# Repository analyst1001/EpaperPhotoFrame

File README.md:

# E-Paper Photo Frame

## Goals
- The main goal is to display photos on a E-paper display so that it looks similar to a photo frame. The displayed photo will change periodically.
- An additional goal is to allow the device to run on a common battery power source so that it can work without plugging into wall power.

## How to use
The script stored in `Software/transform_images.py` can be used to modify images in common format (png, jpg, etc.) to binary blobs which can be copied to a FAT32 partition (formatted with block size 512) on a SD card. These blobs are read by software starting with filename "0.bin", "1.bin", and so on and displayed on the E-paper screen. When a filename "<n>.bin" for some number `n` is not found, the software starts displaying images from "0.bin" again and keeps looping like this.

## Branches
This branch has PCB design to hold all the components for E-paper photo frame with connections to external battery, external E-paper display, external LEDs, and external SD card storage. Additionally it has code that can be flashed to STM32 MCU to use the PCB as an Epaper photo frame.
The branch `development_board` has code to run software on the development board with appropriate connections to external devices.

## MCU interfaces
- SPI interface is used to communicate with SD card and E-paper display.
- UART interface is used to log debug messages. This can be disabled by a C macro to reduce power usage in the final version.
- GPIOs to power on/off BUSY and ERROR LEDs, and SD card.

## Code implementation
1. Initialize the MCU using HAL layer. Configure system clock to use 80MHz. Using the max frequency allows SPI interface to SD card to communicate with max speed. This will allow SD card to be powered on for a shorter amount of time hence reducing the power usage (given that I plan to keep the MCU in low power mode for hours).
2. Initialize LEDs and RTC peripheral. BUSY LED indicates that the MCU is busy using the SD card or the E-paper display. ERROR LED indicates that an irrecoverable error has occurred. RTC peripheral is used to leverage the WakeUp timer in order to wake up the MCU from sleep mode periodically.
3. Initialize SD card and E-paper display.
4. Read data from the file to display and send it to E-paper display. Refresh the display and put it to sleep when the image is displayed.
5. Enable WakeUp interrupt to wake up the processor after given time interval.
6. Configure peripherals to reduce current consumption and put the MCU in Standby/Shutdown mode.

## Current consumption (TBD)

## Future Plans
- Use a data logger to measure instantaneous current consumption value with better resolution.
- Re-write the logic to use interrupt based processing. The SPI based communication can use interrupt based processing where the MCU can be put into low-power sleep mode when waiting for data transmission/reception. Same can be used when waiting for BUSY signal from E-paper display and time delays in the logic.
- Use DMA peripheral to transmit/receive large data blobs (image pixel data). STM32L4 series processor support a feature called Batch Acquisition sub-mode(BAM), as mentioned in Section 2.1.1 of [AN4621](https://www.st.com/resource/en/application_note/an4621-stm32l4-and-stm32l4-ultralowpower-features-overview-stmicroelectronics.pdf), that could allow this.

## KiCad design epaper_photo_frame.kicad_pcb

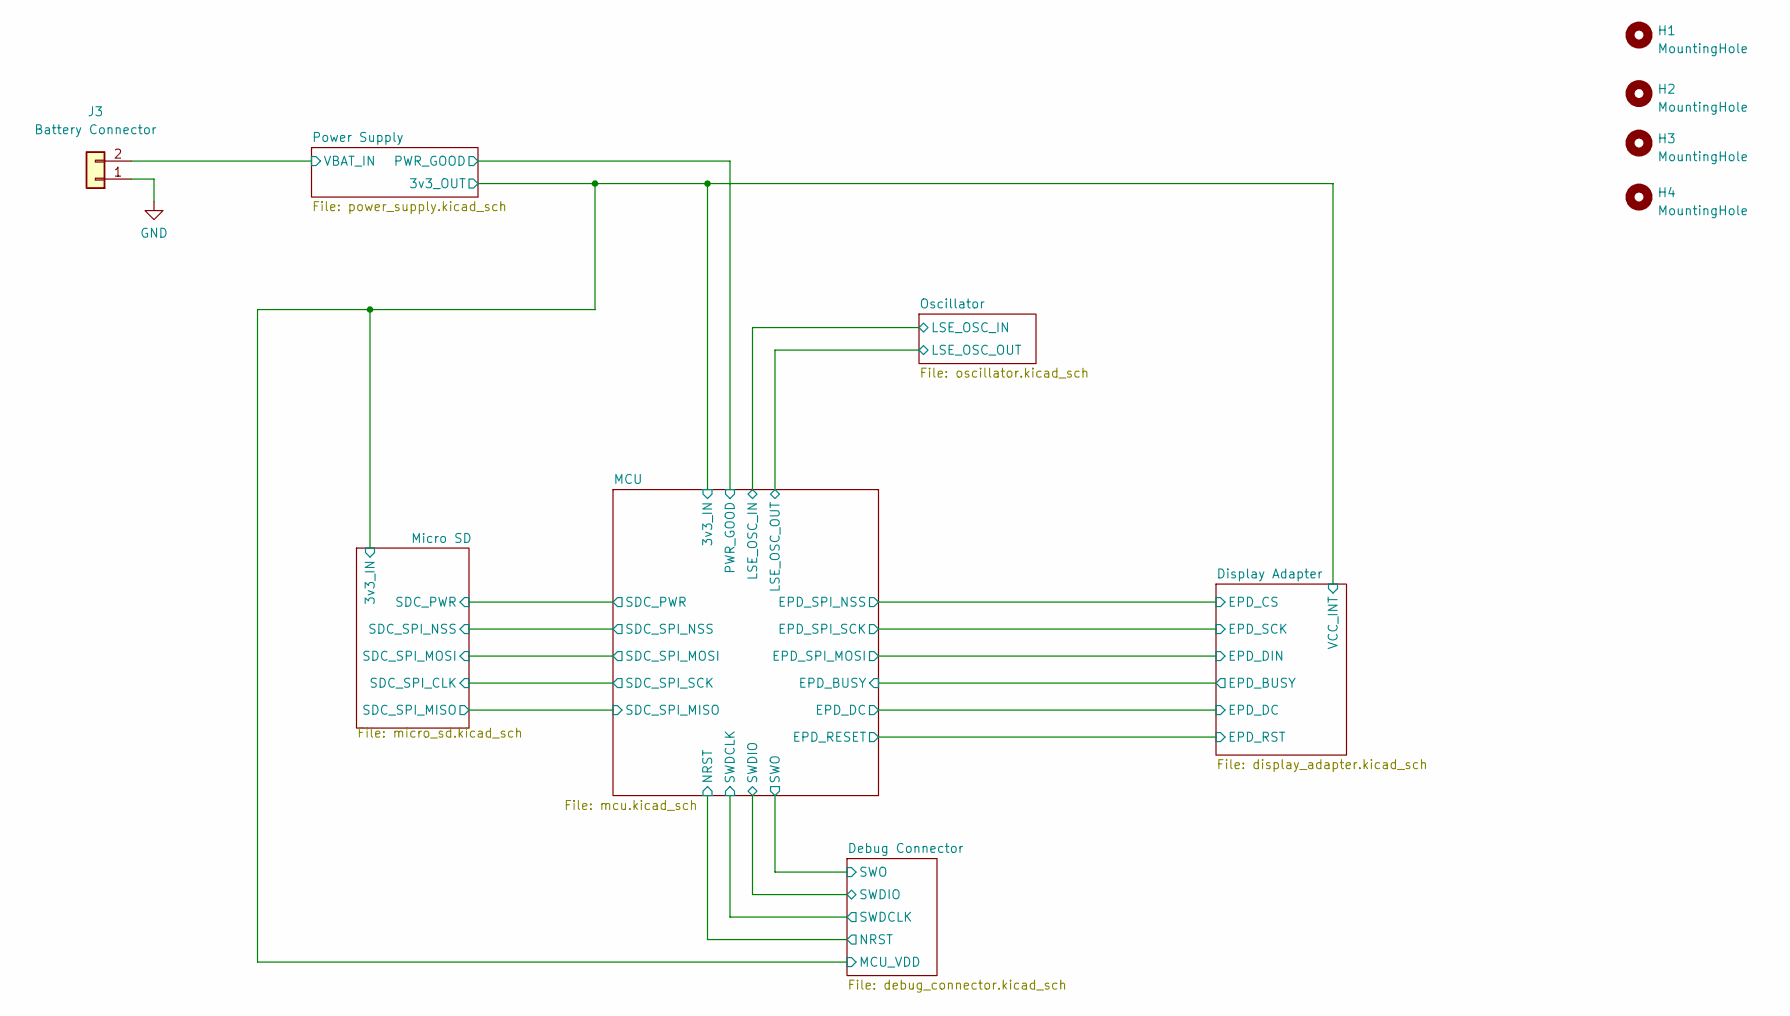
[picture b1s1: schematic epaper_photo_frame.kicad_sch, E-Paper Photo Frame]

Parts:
H1, H2, H3, H4: MountingHole; MountingHole_3.2mm_M3
J3: Battery Connector; JST_PH_B2B-PH-K_1x02_P2.00mm_Vertical

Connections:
/Power Supply/VBAT_IN: J3.2; also elsewhere on the board
GND: J3.1; also elsewhere on the board

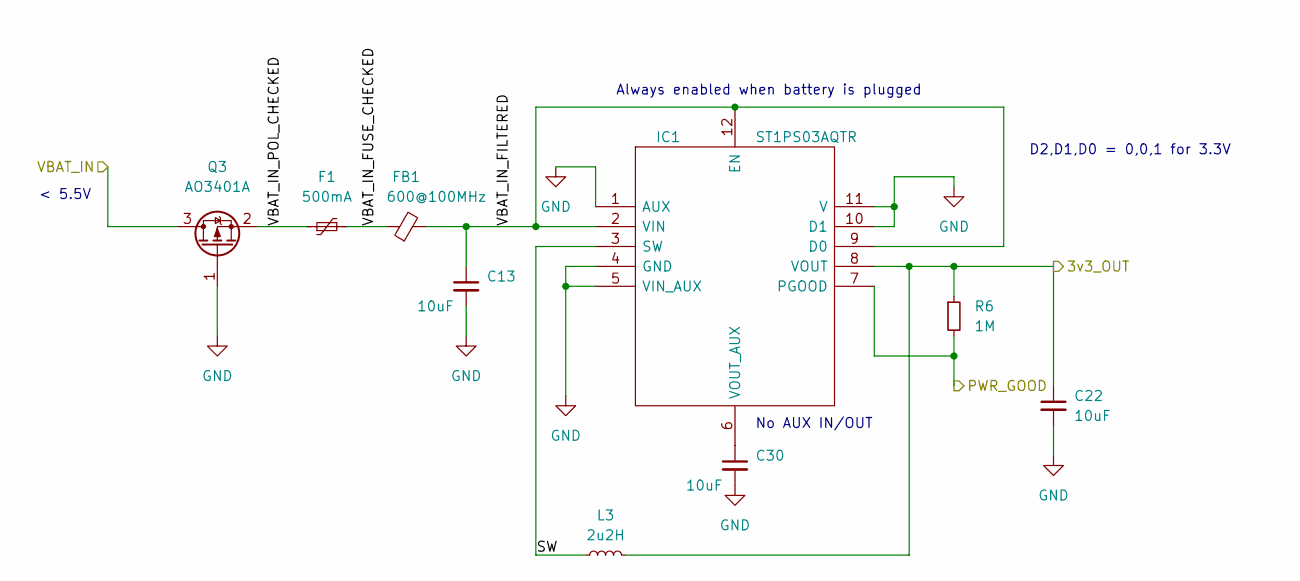
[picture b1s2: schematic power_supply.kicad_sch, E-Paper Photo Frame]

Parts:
C13, C22: 10uF; C_0805_2012Metric; LCSC C15850
C30: 10uF; C_0603_1608Metric; LCSC C96446
F1: 500mA; Fuse_1206_3216Metric; LCSC C69688
FB1: 600@100MHz; L_0805_2012Metric; LCSC C1017
IC1: ST1PS03AQTR; QFN40P170X200X55-12N-D; Manufacturer_Part_Number ST1PS03AQTR; Mouser Part Number 511-ST1PS03AQTR
L3: 2u2H; L_0805_2012Metric; LCSC C370034
Q3: AO3401A; SOT-23; LCSC C15127
R6: 1M; R_0805_2012Metric; LCSC C441966

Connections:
/Debug Connector/MCU_VDD: C22.1, IC1.8 (VOUT), L3.2, R6.1; also elsewhere on the board
/MCU/PWR_GOOD: IC1.7 (PGOOD), R6.2; also elsewhere on the board
/Power Supply/SW: IC1.3 (SW), L3.1
/Power Supply/VBAT_IN: Q3.3 (D); also elsewhere on the board
/Power Supply/VBAT_IN_FILTERED: C13.1, FB1.2, IC1.2 (VIN), IC1.9 (D0), IC1.12 (EN)
/Power Supply/VBAT_IN_FUSE_CHECKED: F1.2, FB1.1
/Power Supply/VBAT_IN_POL_CHECKED: F1.1, Q3.2 (S)
GND: C13.2, C22.2, C30.2, IC1.1 (AUX), IC1.4 (GND), IC1.5 (VIN_AUX), IC1.10 (D1), IC1.11 (V), Q3.1 (G); also elsewhere on the board
unnamed: C30.1, IC1.6 (VOUT_AUX)

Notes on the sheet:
D2,D1,D0 = 0,0,1 for 3.3V
No AUX IN/OUT
< 5.5V
Always enabled when battery is plugged

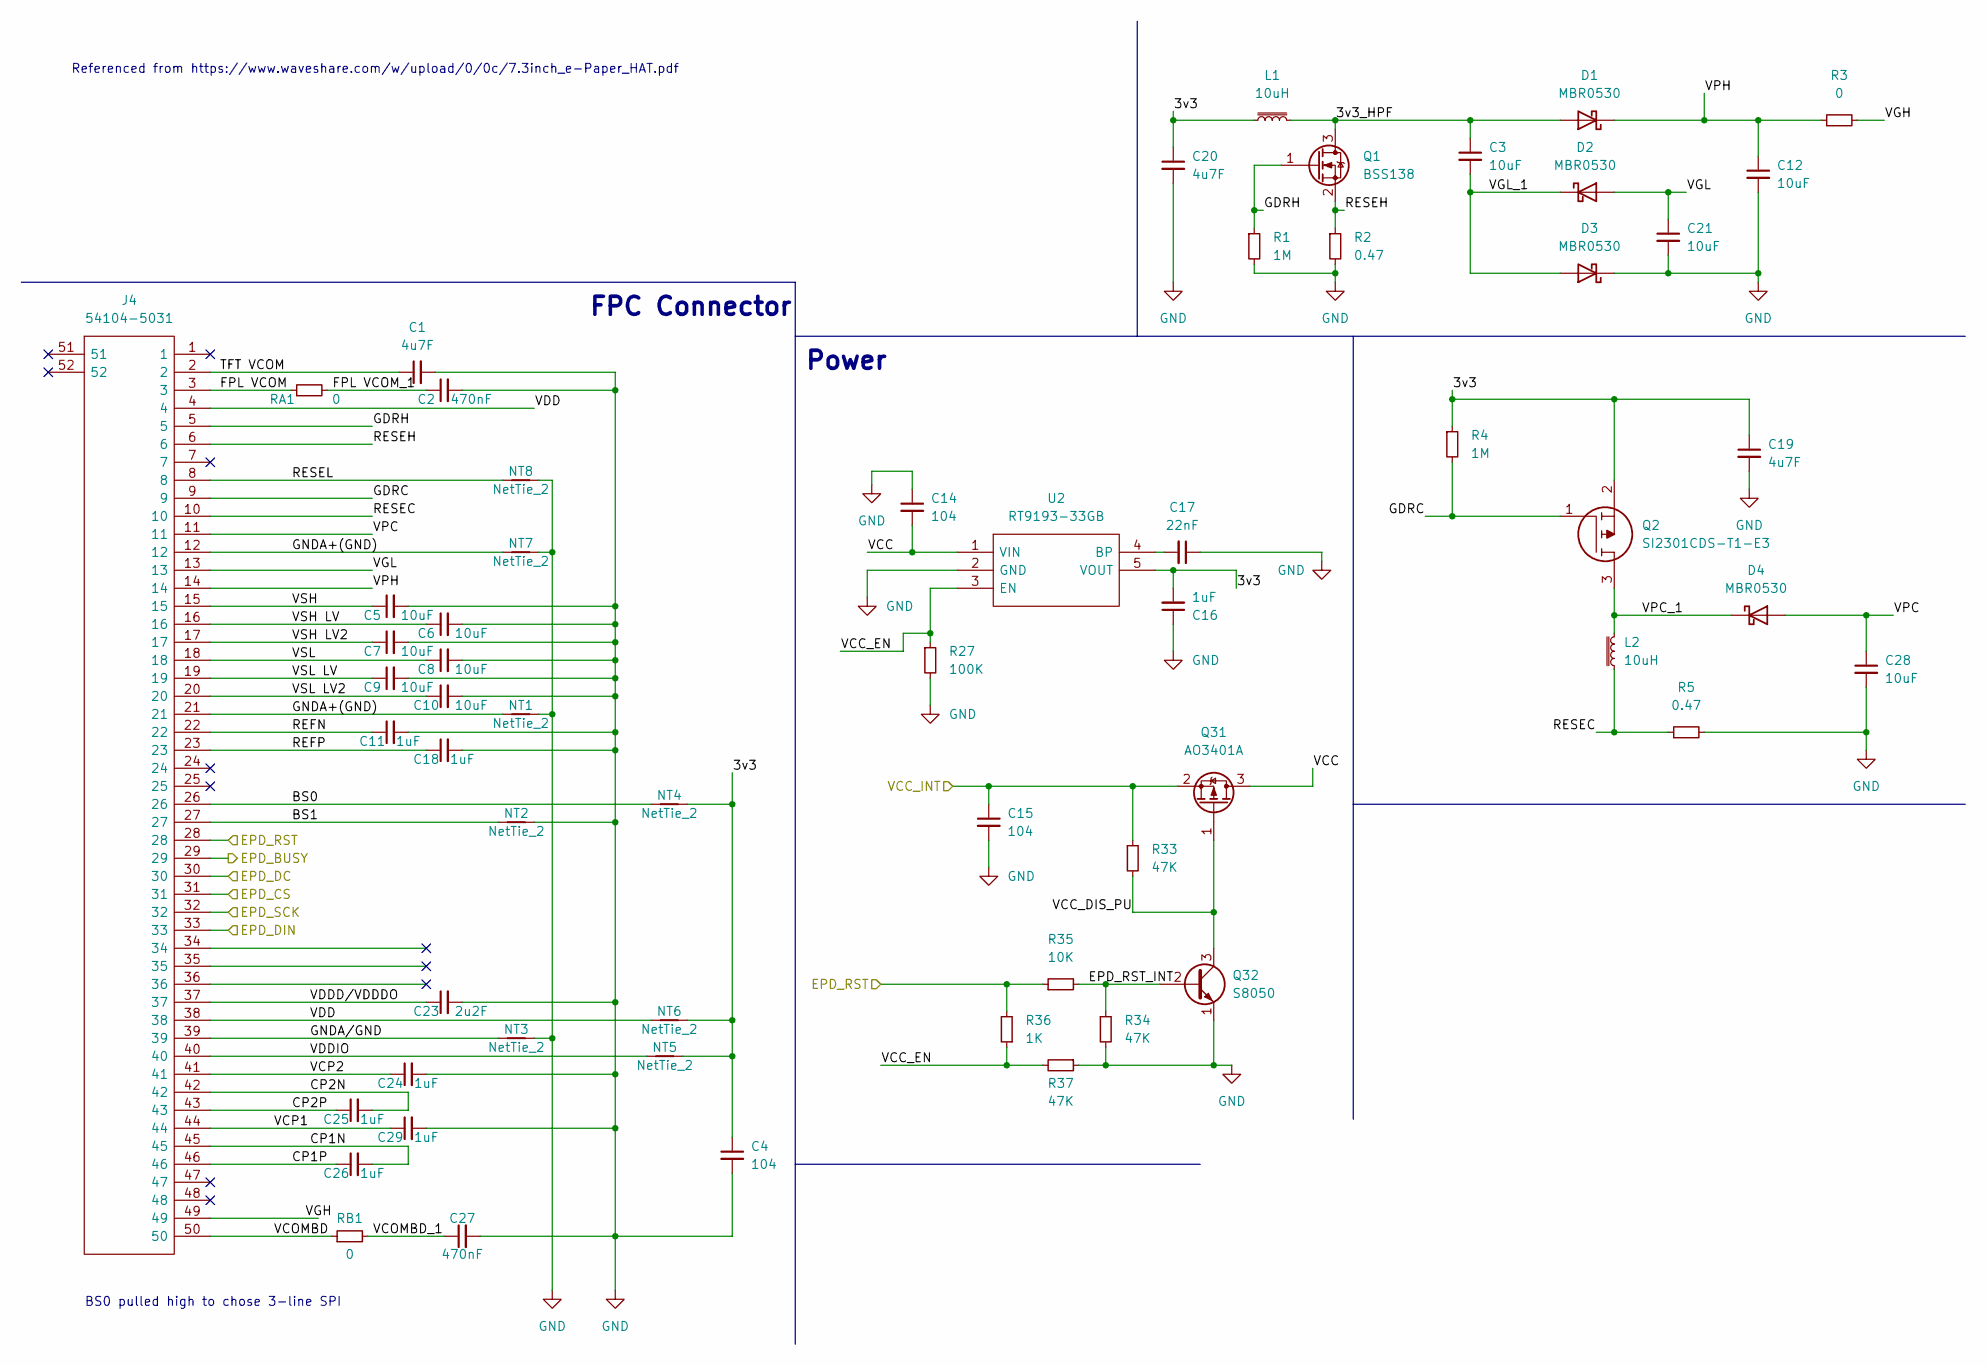
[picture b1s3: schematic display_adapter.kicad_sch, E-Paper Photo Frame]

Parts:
C1, C19, C20: 4u7F; C_0603_1608Metric; MAX Voltage 10V; LCSC C19666
C2, C27: 470nF; C_0603_1608Metric; MAX Voltage 25V; LCSC C1623
C3, C5, C6, C7, C8, C9, C10, C12, C21, C28: 10uF; C_0603_1608Metric; MAX Voltage 25V; LCSC C96446
C4: 104; C_0603_1608Metric; LCSC C14663
C11, C18, C24, C25, C26, C29: 1uF; C_0603_1608Metric; MAX Voltage 10V; LCSC C15849
C14, C15: 104; C_0805_2012Metric; LCSC C49678
C16: 1uF; C_0805_2012Metric; LCSC C28323
C17: 22nF; C_0805_2012Metric; LCSC C1729
C23: 2u2F; C_0603_1608Metric; MAX Voltage 6V; LCSC C23630
D1, D2, D3, D4: MBR0530; D_SOD-123; LCSC C18863
J4: 54104-5031; 541045031; Manufacturer_Part_Number 54104-5031; Mouser Part Number 538-54104-5031
L1, L2: 10uH; INDPM4040X200N; LCSC C82398
NT1, NT2, NT3, NT4, NT5, NT6, NT7, NT8: NetTie_2; NetTie-2_SMD_Pad0.5mm
Q1: BSS138; SOT-23; LCSC C82045
Q2: SI2301CDS-T1-E3; SOT95P237X112-3N; Manufacturer_Part_Number SI2301CDS-T1-E3; Mouser Part Number 781-SI2301CDS-E3
Q31: AO3401A; SOT-23; LCSC C15127
Q32: S8050; SOT-23-3; LCSC C2150
R1, R4: 1M; R_0805_2012Metric; LCSC C441966
R2, R5: 0.47; R_0805_2012Metric; LCSC C491238
R3: 0; R_0805_2012Metric; LCSC C17477
R27: 100K; R_0805_2012Metric; LCSC C149504
R33, R34: 47K; R_0805_2012Metric; LCSC C17713
R35: 10K; R_0805_2012Metric; LCSC C510098
R36: 1K; R_0805_2012Metric; LCSC C17513
R37: 47K; R_0805_2012Metric; LCSC C2073899
RA1: 0; R_0805_2012Metric; LCSC C17477
RB1: 0; R_0805_2012Metric; LCSC C17477
U2: RT9193-33GB; SOT94P279X130-5N; Manufacturer_Part_Number RT9193-33GB; LCSC C15651

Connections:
/Debug Connector/MCU_VDD: C15.1, Q31.2 (S), R33.1; also elsewhere on the board
/Display Adapter/3v3: C4.1, C16.2, C19.1, C20.1, L1.1, NT4.2, NT5.2, NT6.2, Q2.2, R4.1, U2.5 (VOUT)
/Display Adapter/3v3_HPF: C3.1, D1.2 (A), L1.2, Q1.3 (D)
/Display Adapter/BS0: J4.26, NT4.1
/Display Adapter/BS1: J4.27, NT2.1
/Display Adapter/CP1N: C26.2, J4.45
/Display Adapter/CP1P: C26.1, J4.46
/Display Adapter/CP2N: C25.2, J4.42
/Display Adapter/CP2P: C25.1, J4.43
/Display Adapter/EPD_BUSY: J4.29; also elsewhere on the board
/Display Adapter/EPD_CS: J4.31; also elsewhere on the board
/Display Adapter/EPD_DC: J4.30; also elsewhere on the board
/Display Adapter/EPD_DIN: J4.33; also elsewhere on the board
/Display Adapter/EPD_RST: J4.28, R35.1, R36.2; also elsewhere on the board
/Display Adapter/EPD_RST_INT: Q32.2 (B), R34.1, R35.2
/Display Adapter/EPD_SCK: J4.32; also elsewhere on the board
/Display Adapter/FPL VCOM: J4.3, RA1.1
/Display Adapter/FPL VCOM_1: C2.1, RA1.2
/Display Adapter/GDRC: J4.9, Q2.1, R4.2
/Display Adapter/GDRH: J4.5, Q1.1 (G), R1.1
/Display Adapter/GNDA+(GND): J4.12, J4.21, NT1.1, NT7.1
/Display Adapter/GNDA/GND: J4.39, NT3.1
/Display Adapter/REFN: C11.1, J4.22
/Display Adapter/REFP: C18.1, J4.23
/Display Adapter/RESEC: J4.10, L2.1, R5.1
/Display Adapter/RESEH: J4.6, Q1.2 (S), R2.1
/Display Adapter/RESEL: J4.8, NT8.1
/Display Adapter/TFT VCOM: C1.1, J4.2
/Display Adapter/VCC: C14.2, Q31.3 (D), U2.1 (VIN)
/Display Adapter/VCC_DIS_PU: Q31.1 (G), Q32.3 (C), R33.2
/Display Adapter/VCC_EN: R27.1, R36.1, R37.2, U2.3 (EN)
/Display Adapter/VCOMBD: J4.50, RB1.1
/Display Adapter/VCOMBD_1: C27.1, RB1.2
/Display Adapter/VCP1: C29.1, J4.44
/Display Adapter/VCP2: C24.1, J4.41
/Display Adapter/VDD: J4.4, J4.38, NT6.1
/Display Adapter/VDDD/VDDDO: C23.1, J4.37
/Display Adapter/VDDIO: J4.40, NT5.1
/Display Adapter/VGH: J4.49, R3.2
/Display Adapter/VGL: C21.1, D2.2 (A), J4.13
/Display Adapter/VGL_1: C3.2, D2.1 (K), D3.2 (A)
/Display Adapter/VPC: C28.1, D4.2 (A), J4.11
/Display Adapter/VPC_1: D4.1 (K), L2.2, Q2.3
/Display Adapter/VPH: C12.1, D1.1 (K), J4.14, R3.1
/Display Adapter/VSH: C5.1, J4.15
/Display Adapter/VSH LV: C6.1, J4.16
/Display Adapter/VSH LV2: C7.1, J4.17
/Display Adapter/VSL: C8.1, J4.18
/Display Adapter/VSL LV: C9.1, J4.19
/Display Adapter/VSL LV2: C10.1, J4.20
GND: C1.2, C2.2, C4.2, C5.2, C6.2, C7.2, C8.2, C9.2, C10.2, C11.2, C12.2, C14.1, C15.2, C16.1, C17.1, C18.2, C19.2, C20.2, C21.2, C23.2, C24.2, C27.2, C28.2, C29.2, D3.1 (K), NT1.2, NT2.2, NT3.2, NT7.2, NT8.2, Q32.1 (E), R1.2, R2.2, R5.2, R27.2, R34.2, R37.1, U2.2 (GND); also elsewhere on the board
unnamed: C17.2, U2.4 (BP)

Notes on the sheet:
FPC Connector
BS0 pulled high to chose 3-line SPI
Power
Referenced from https://www.waveshare.com/w/upload/0/0c/7.3inch_e-Paper_HAT.pdf

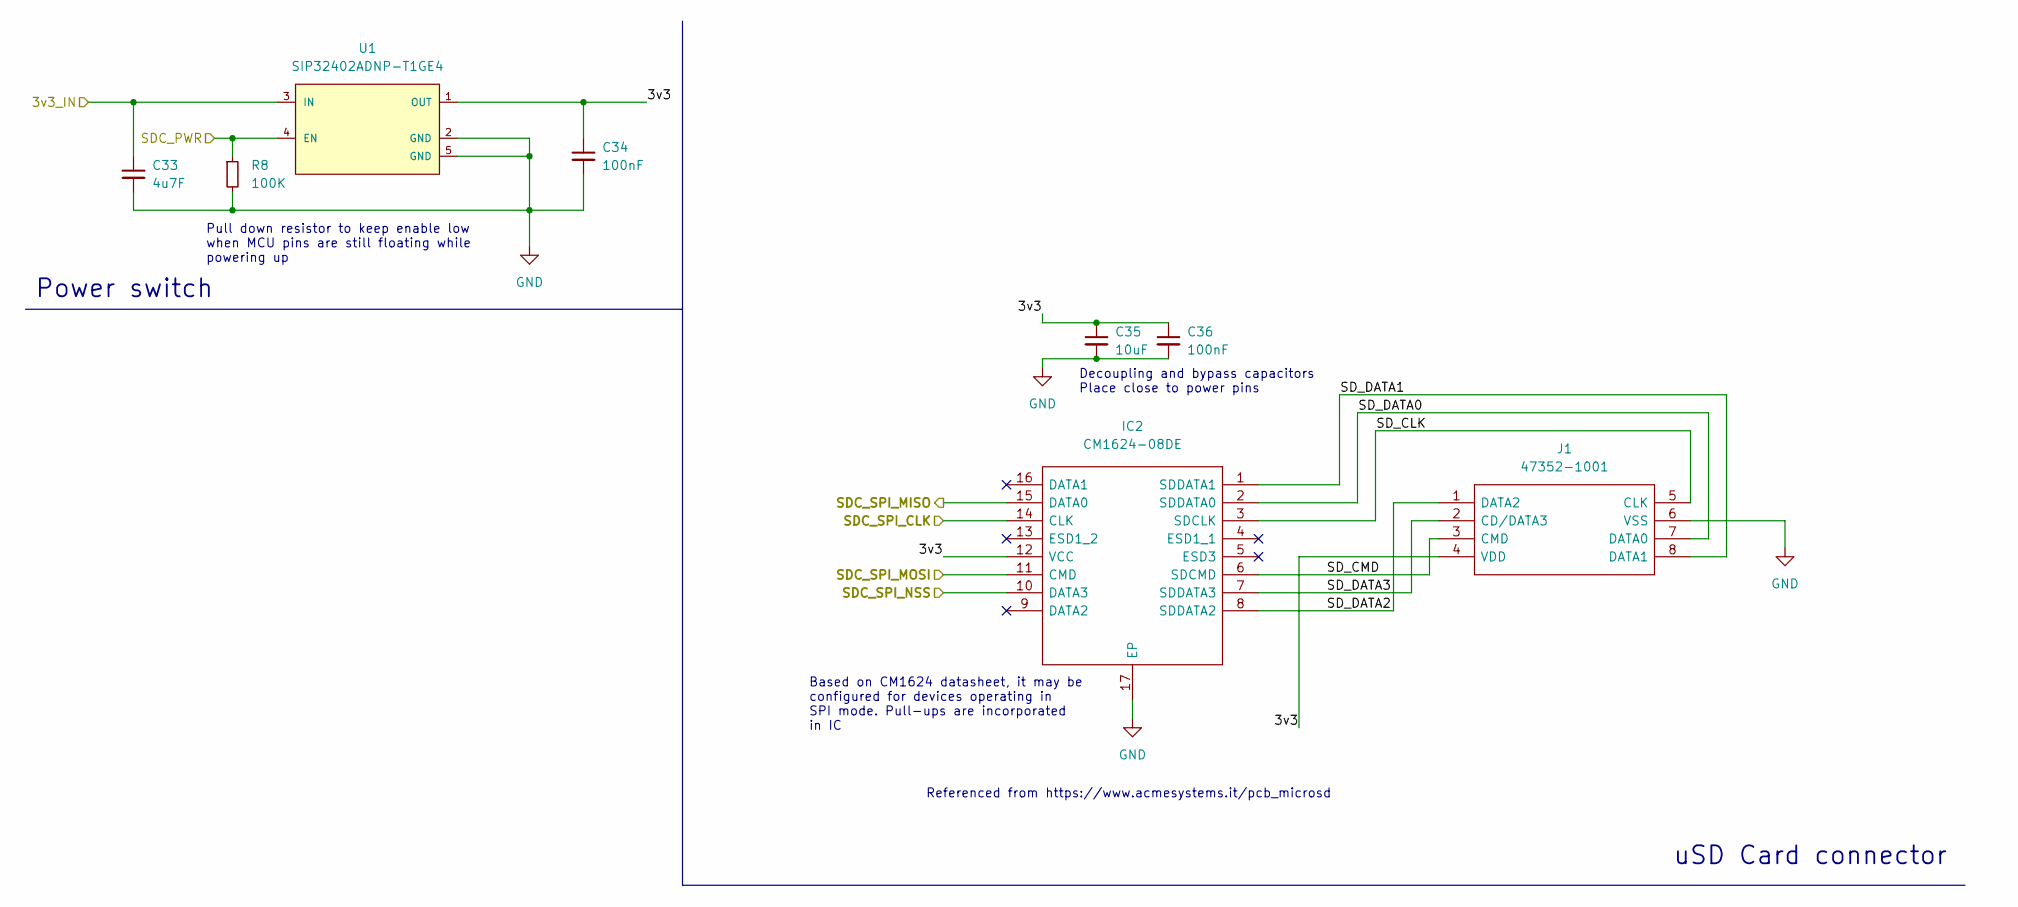
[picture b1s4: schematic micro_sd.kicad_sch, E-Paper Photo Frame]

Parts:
C33: 4u7F; C_0805_2012Metric; LCSC C1779
C34: 100nF; C_0805_2012Metric; LCSC C49678
C35: 10uF; C_0603_1608Metric; LCSC C96446
C36: 100nF; C_0603_1608Metric; LCSC C14663
IC2: CM1624-08DE; SON40P135X330X55-17N; Manufacturer_Part_Number CM1624-08DE; Mouser Part Number 748-CM1624-08DE
J1: 47352-1001; Manufacturer_Part_Number 47352-1001; Mouser Part Number 538-47352-1001
R8: 100K; R_0805_2012Metric; LCSC C149504
U1: SIP32402ADNP-T1GE4; Vishay-T16-0143-04_2016-C-MFG; mouser part number 78-SIP32402ADNPT1GE4; digikey description IC PWR SWITCH N-CHAN 1:1 4TDFN

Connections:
/Debug Connector/MCU_VDD: C33.1, U1.3 (IN); also elsewhere on the board
/MCU/SDC_PWR: R8.1, U1.4 (EN); also elsewhere on the board
/MCU/SDC_SPI_MISO: IC2.15 (DATA0); also elsewhere on the board
/MCU/SDC_SPI_MOSI: IC2.11 (CMD); also elsewhere on the board
/MCU/SDC_SPI_NSS: IC2.10 (DATA3); also elsewhere on the board
/MCU/SDC_SPI_SCK: IC2.14 (CLK); also elsewhere on the board
/Micro SD/3v3: C34.1, C35.1, C36.1, IC2.12 (VCC), J1.4 (VDD), U1.1 (OUT)
/Micro SD/SD_CLK: IC2.3 (SDCLK), J1.5 (CLK)
/Micro SD/SD_CMD: IC2.6 (SDCMD), J1.3 (CMD)
/Micro SD/SD_DATA0: IC2.2 (SDDATA0), J1.7 (DATA0)
/Micro SD/SD_DATA1: IC2.1 (SDDATA1), J1.8 (DATA1)
/Micro SD/SD_DATA2: IC2.8 (SDDATA2), J1.1 (DATA2)
/Micro SD/SD_DATA3: IC2.7 (SDDATA3), J1.2 (CD/DATA3)
GND: C33.2, C34.2, C35.2, C36.2, IC2.17 (EP), J1.6 (VSS), R8.2, U1.2 (GND), U1.5 (GND); also elsewhere on the board

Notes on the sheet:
Referenced from https://www.acmesystems.it/pcb_microsd
Power switch
Pull down resistor to keep enable low when MCU pins are still floating while powering up
uSD Card connector
Decoupling and bypass capacitors Place close to power pins
Based on CM1624 datasheet, it may be configured for devices operating in SPI mode. Pull-ups are incorporated in IC

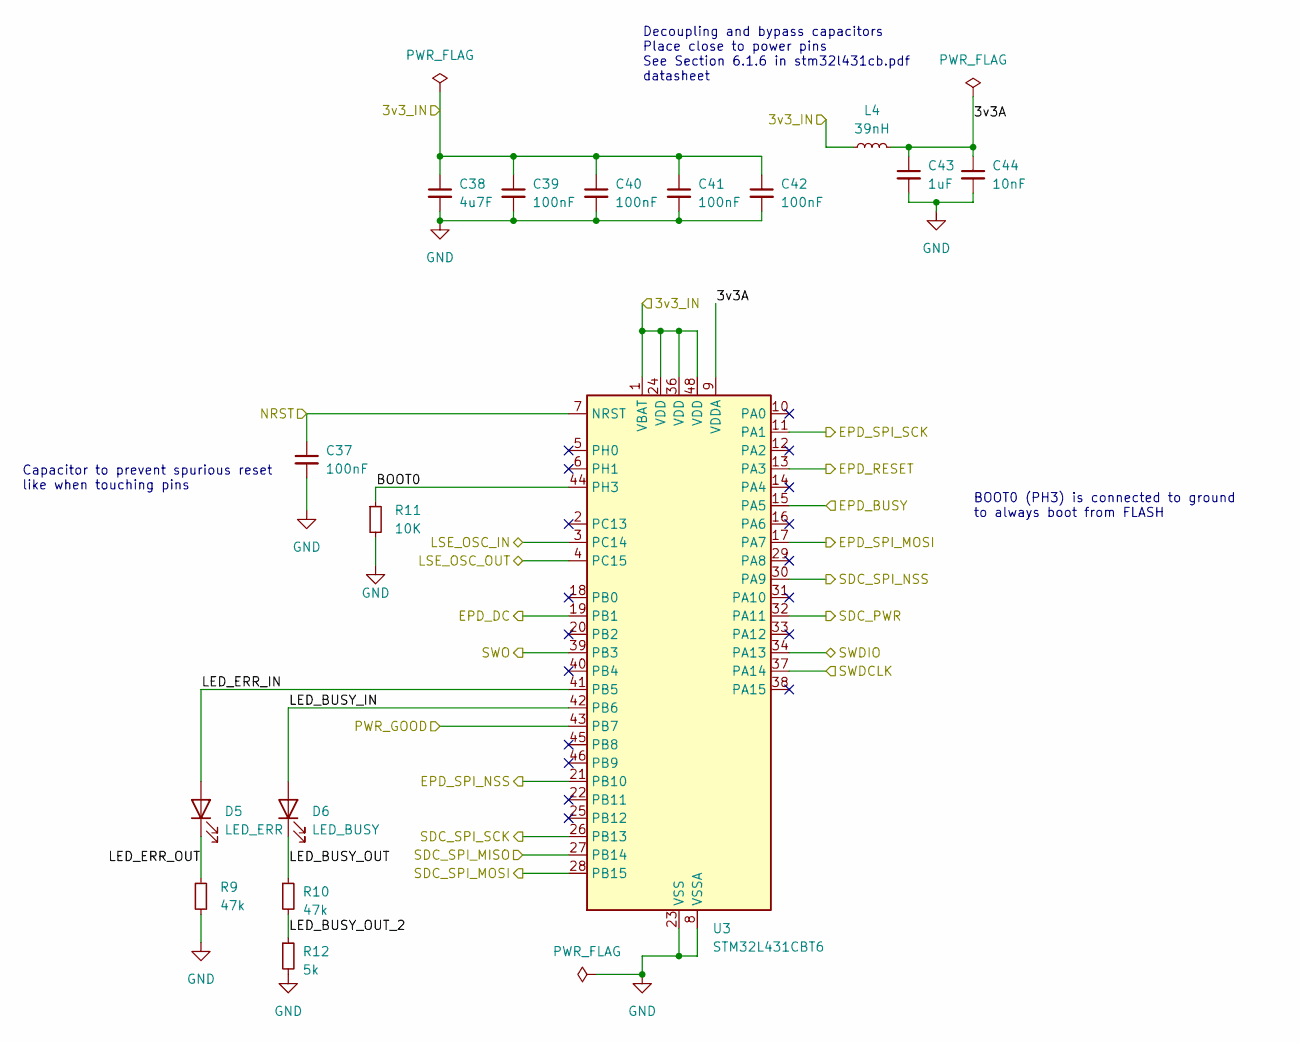
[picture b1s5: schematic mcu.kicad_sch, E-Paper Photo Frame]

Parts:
C37, C39, C40, C41, C42: 100nF; C_0603_1608Metric; LCSC C14663
C38: 4u7F; C_0603_1608Metric; LCSC C19666
C43: 1uF; C_0603_1608Metric; LCSC C15849
C44: 10nF; C_0603_1608Metric; LCSC C57112
D5: LED_ERR; LED_D3.0mm
D6: LED_BUSY; LED_D3.0mm
L4: 39nH; L_0402_1005Metric; LCSC C440213
R9, R10: 47k; R_1210_3225Metric; LCSC C230465
R11: 10K; R_0805_2012Metric; LCSC C510098
R12: 5k; R_1206_3216Metric; LCSC C870818
U3: STM32L431CBT6; LQFP-48_7x7mm_P0.5mm; LCSC C277951

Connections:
/Debug Connector/MCU_VDD: C38.1, C39.1, C40.1, C41.1, C42.1, L4.1, U3.1 (VBAT), U3.24 (VDD), U3.36 (VDD), U3.48 (VDD); also elsewhere on the board
/Debug Connector/NRST: C37.1, U3.7 (NRST); also elsewhere on the board
/Debug Connector/SWDCLK: U3.37 (PA14); also elsewhere on the board
/Debug Connector/SWDIO: U3.34 (PA13); also elsewhere on the board
/Debug Connector/SWO: U3.39 (PB3); also elsewhere on the board
/Display Adapter/EPD_BUSY: U3.15 (PA5); also elsewhere on the board
/Display Adapter/EPD_CS: U3.21 (PB10); also elsewhere on the board
/Display Adapter/EPD_DC: U3.19 (PB1); also elsewhere on the board
/Display Adapter/EPD_DIN: U3.17 (PA7); also elsewhere on the board
/Display Adapter/EPD_RST: U3.13 (PA3); also elsewhere on the board
/Display Adapter/EPD_SCK: U3.11 (PA1); also elsewhere on the board
/MCU/3v3A: C43.1, C44.1, L4.2, U3.9 (VDDA)
/MCU/BOOT0: R11.1, U3.44 (PH3)
/MCU/LED_BUSY_IN: D6.2 (A), U3.42 (PB6)
/MCU/LED_BUSY_OUT: D6.1 (K), R10.1
/MCU/LED_BUSY_OUT_2: R10.2, R12.1
/MCU/LED_ERR_IN: D5.2 (A), U3.41 (PB5)
/MCU/LED_ERR_OUT: D5.1 (K), R9.1
/MCU/LSE_OSC_IN: U3.3 (PC14); also elsewhere on the board
/MCU/LSE_OSC_OUT: U3.4 (PC15); also elsewhere on the board
/MCU/PWR_GOOD: U3.43 (PB7); also elsewhere on the board
/MCU/SDC_PWR: U3.32 (PA11); also elsewhere on the board
/MCU/SDC_SPI_MISO: U3.27 (PB14); also elsewhere on the board
/MCU/SDC_SPI_MOSI: U3.28 (PB15); also elsewhere on the board
/MCU/SDC_SPI_NSS: U3.30 (PA9); also elsewhere on the board
/MCU/SDC_SPI_SCK: U3.26 (PB13); also elsewhere on the board
GND: C37.2, C38.2, C39.2, C40.2, C41.2, C42.2, C43.2, C44.2, R9.2, R11.2, R12.2, U3.8 (VSSA), U3.23 (VSS), U3.35 (VSS), U3.47 (VSS); also elsewhere on the board

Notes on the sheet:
Capacitor to prevent spurious reset like when touching pins
BOOT0 (PH3) is connected to ground to always boot from FLASH
Decoupling and bypass capacitors Place close to power pins See Section 6.1.6 in stm32l431cb.pdf datasheet

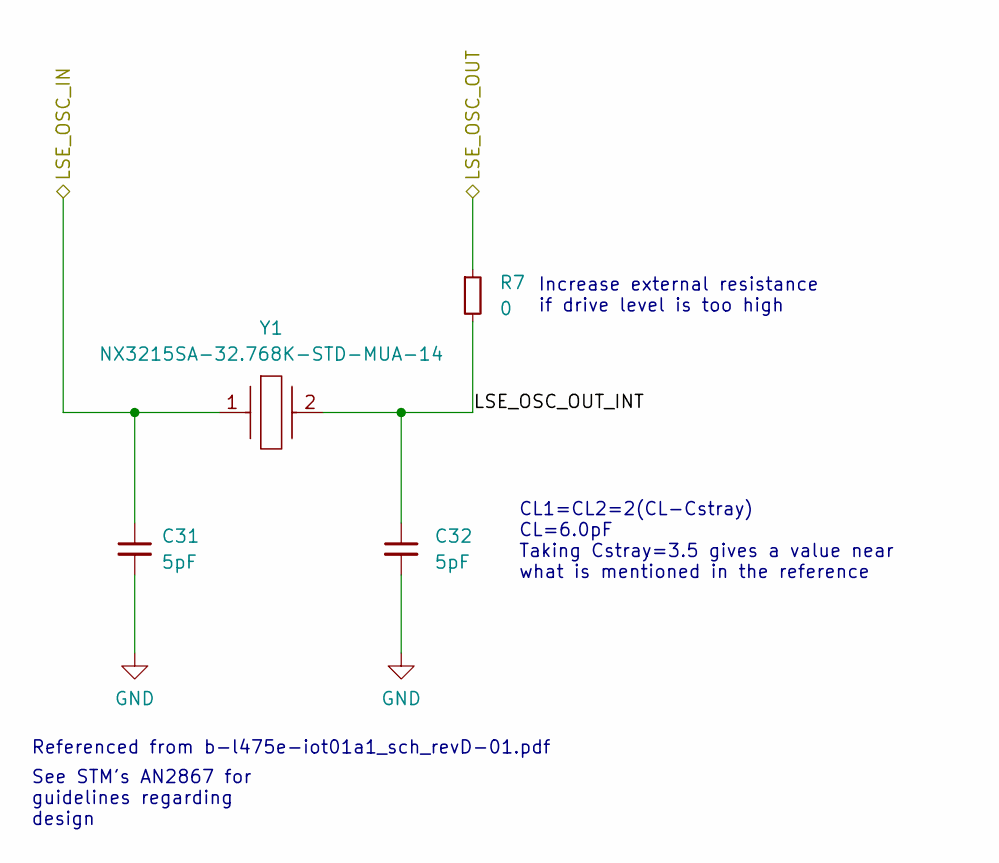
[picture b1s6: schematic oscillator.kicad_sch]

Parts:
C31, C32: 5pF; C_0402_1005Metric; LCSC C730435
R7: 0; R_0402_1005Metric; LCSC C17168
Y1: NX3215SA-32.768K-STD-MUA-14; NX3215SA32768KSTDMUA14; Manufacturer_Part_Number NX3215SA-32.768K-STD-MUA-14; Mouser Part Number 344-NX3215SA32768K14

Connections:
/MCU/LSE_OSC_IN: C31.1, Y1.1; also elsewhere on the board
/MCU/LSE_OSC_OUT: R7.1; also elsewhere on the board
/Oscillator/LSE_OSC_OUT_INT: C32.1, R7.2, Y1.2
GND: C31.2, C32.2; also elsewhere on the board

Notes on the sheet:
Referenced from b-l475e-iot01a1_sch_revD-01.pdf
See STM's AN2867 for guidelines regarding design
Increase external resistance if drive level is too high
CL1=CL2=2(CL-Cstray) CL=6.0pF Taking Cstray=3.5 gives a value near what is mentioned in the reference

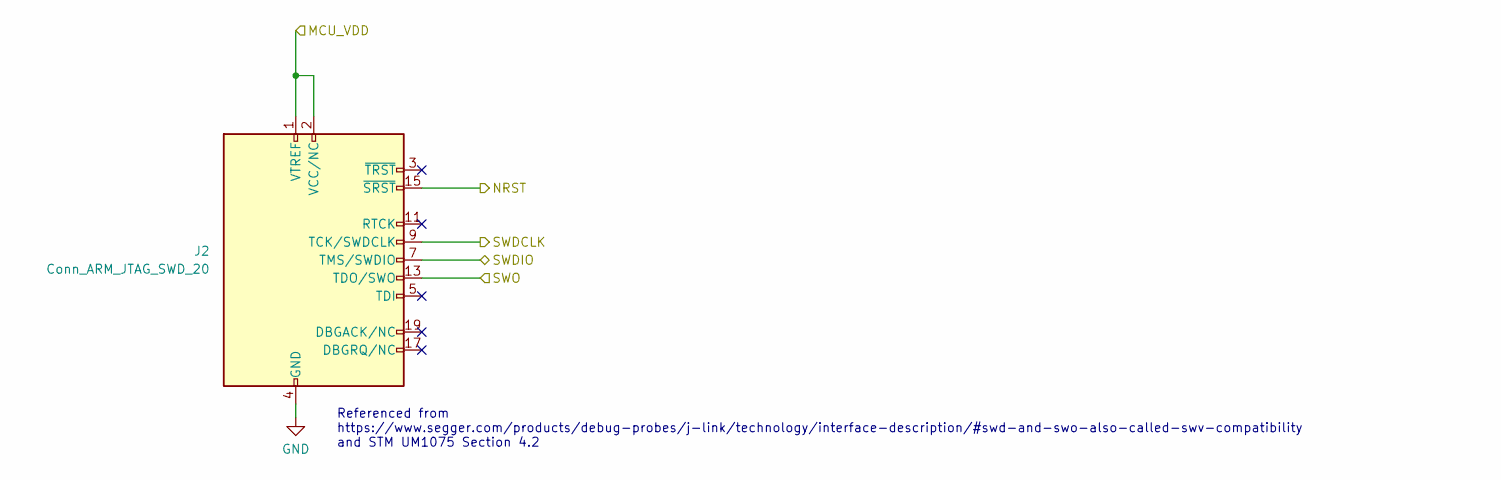
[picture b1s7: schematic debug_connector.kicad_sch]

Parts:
J2: Conn_ARM_JTAG_SWD_20; PinHeader_2x10_P2.54mm_Vertical

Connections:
/Debug Connector/MCU_VDD: J2.1 (VTREF), J2.2 (VCC/NC); also elsewhere on the board
/Debug Connector/NRST: J2.15 (~SRST); also elsewhere on the board
/Debug Connector/SWDCLK: J2.9 (TCK/SWDCLK); also elsewhere on the board
/Debug Connector/SWDIO: J2.7 (TMS/SWDIO); also elsewhere on the board
/Debug Connector/SWO: J2.13 (TDO/SWO); also elsewhere on the board
GND: J2.4 (GND), J2.6 (GND), J2.8 (GND), J2.10 (GND), J2.12 (GND), J2.14 (GND), J2.16 (GND), J2.18 (GND), J2.20 (GND); also elsewhere on the board

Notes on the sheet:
Referenced from https://www.segger.com/products/debug-probes/j-link/technology/interface-description/#swd-and-swo-also-called-swv-compatibility and STM UM1075 Section 4.2

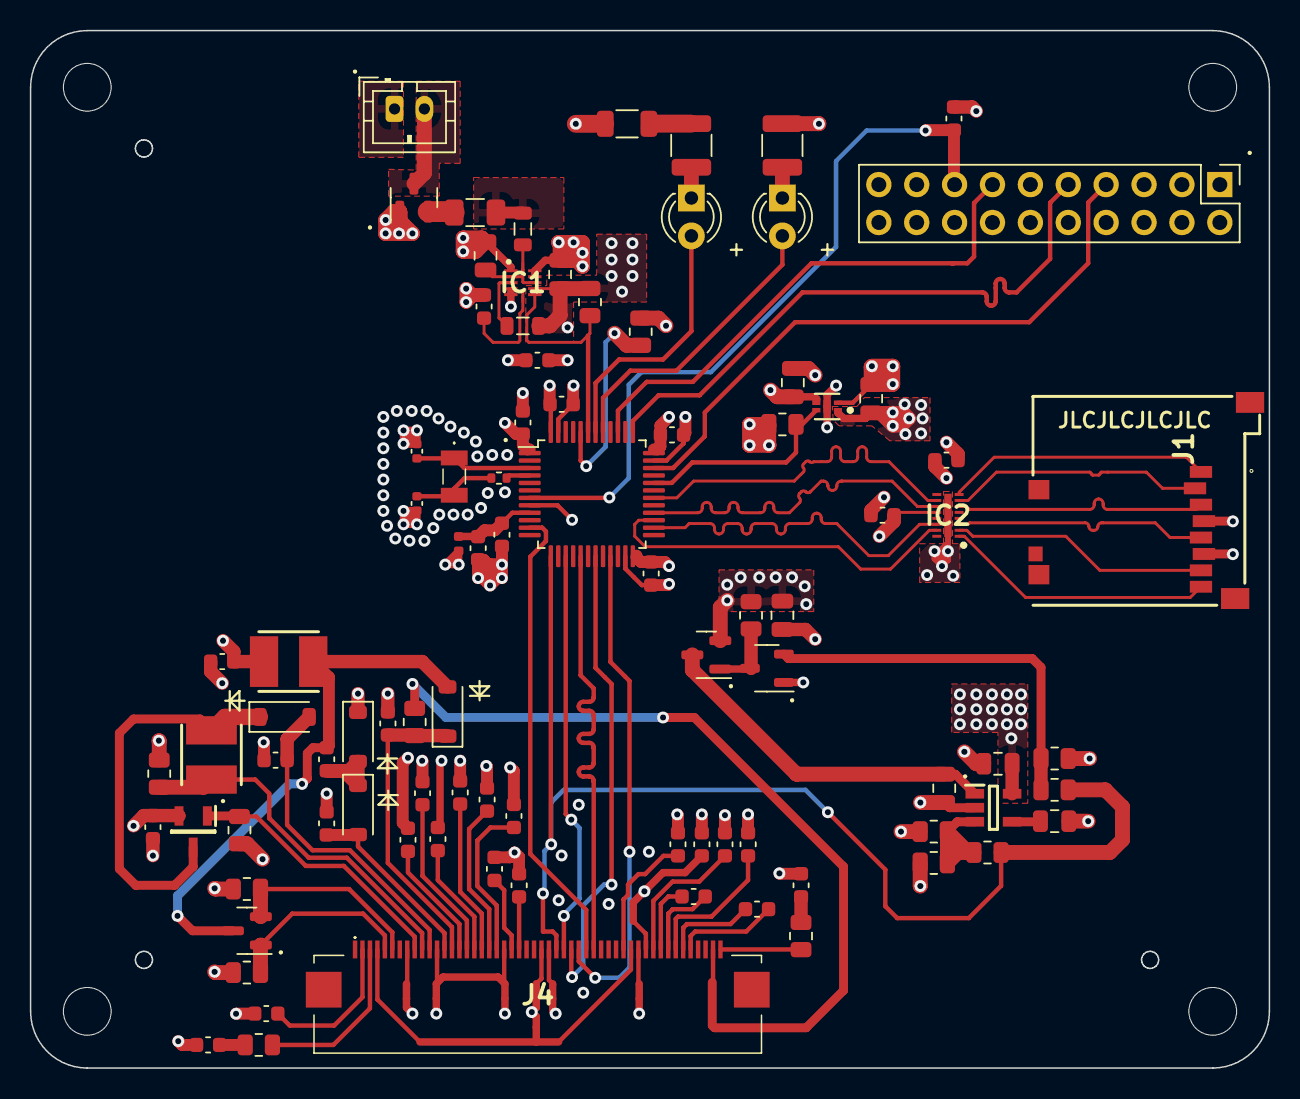
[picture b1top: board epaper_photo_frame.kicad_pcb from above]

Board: 4 copper layers, 83.1 x 69.5 mm, 103 parts (0 on the bottom side), 85 nets.

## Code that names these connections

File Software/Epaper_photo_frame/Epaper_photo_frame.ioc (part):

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Mcu.Name=STM32L431C(B-C)Tx
Mcu.Package=LQFP48
Mcu.UserName=STM32L431CBTx
PA1.GPIOParameters=GPIO_Label
PA1.GPIO_Label=EPD_SPI_SCK
PA1.Mode=Simplex_Bidirectional_Master
PA1.Signal=SPI1_SCK
PA11.GPIOParameters=GPIO_Label
PA11.GPIO_Label=SDC_PWR
PA11.Signal=GPIO_Output
PA13\ (JTMS-SWDIO).Mode=Trace_Asynchronous_SW
PA13\ (JTMS-SWDIO).Signal=SYS_JTMS-SWDIO
PA14\ (JTCK-SWCLK).Mode=Trace_Asynchronous_SW
PA14\ (JTCK-SWCLK).Signal=SYS_JTCK-SWCLK
PA3.GPIOParameters=GPIO_Label
PA3.GPIO_Label=EPD_RESET
PA3.Signal=GPIO_Output
PA5.GPIOParameters=GPIO_Label
PA5.GPIO_Label=EPD_BUSY
PA5.Signal=GPIO_Output
PA7.GPIOParameters=GPIO_Label
PA7.GPIO_Label=EPD_SPI_MOSI
PA7.Mode=Simplex_Bidirectional_Master
PA7.Signal=SPI1_MOSI
PA9.GPIOParameters=GPIO_Label
PA9.GPIO_Label=SDC_SPI_NSS
PA9.Signal=GPIO_Output
PB1.GPIOParameters=GPIO_Label
PB1.GPIO_Label=EPD_DC
PB1.Signal=GPIO_Output
PB10.GPIOParameters=GPIO_Label
PB10.GPIO_Label=EPD_SPI_NSS
PB10.Signal=GPIO_Output
PB13.GPIOParameters=GPIO_Label
PB13.GPIO_Label=SDC_SPI_SCK
PB13.Mode=Full_Duplex_Master
PB13.Signal=SPI2_SCK
PB14.GPIOParameters=GPIO_Label
PB14.GPIO_Label=SDC_SPI_MISO
PB14.Mode=Full_Duplex_Master
PB14.Signal=SPI2_MISO
PB15.GPIOParameters=GPIO_Label
PB15.GPIO_Label=SDC_SPI_MOSI
PB15.Mode=Full_Duplex_Master
PB15.Signal=SPI2_MOSI
PB3\ (JTDO-TRACESWO).Mode=Trace_Asynchronous_SW
PB3\ (JTDO-TRACESWO).Signal=SYS_JTDO-SWO
PB5.GPIOParameters=GPIO_Label
PB5.GPIO_Label=LED_ERR
PB5.Signal=GPIO_Output
PB6.GPIOParameters=GPIO_Label
PB6.GPIO_Label=LED_BUSY
PB6.Signal=GPIO_Output
PB7.GPIOParameters=GPIO_Label
PB7.GPIO_Label=PWR_GOOD
PB7.Signal=GPIO_Input
PC14-OSC32_IN\ (PC14).GPIOParameters=GPIO_Label
PC14-OSC32_IN\ (PC14).GPIO_Label=LSE_OSC_IN
PC14-OSC32_IN\ (PC14).Mode=LSE-External-Oscillator
PC14-OSC32_IN\ (PC14).Signal=RCC_OSC32_IN
PC15-OSC32_OUT\ (PC15).GPIOParameters=GPIO_Label
PC15-OSC32_OUT\ (PC15).GPIO_Label=LSE_OSC_OUT
PC15-OSC32_OUT\ (PC15).Mode=LSE-External-Oscillator
PC15-OSC32_OUT\ (PC15).Signal=RCC_OSC32_OUT
RCC.HSE_VALUE=8000000
RCC.SYSCLKFreq_VALUE=80000000
RCC.SYSCLKSource=RCC_SYSCLKSOURCE_PLLCLK
board=custom

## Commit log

2022-12-20 Initial commit for MCU code
2022-12-21 Update README. Add illustration for connectivity among components
2022-12-30 Add high side load switch to power off SD card when MCU sleeps
    Add code to control GPIO pin which enables/disables power to SD card
    Change sequence for SD card init and de-init code so that it is powered
    on only for as long as required
    Update README with new observations
2023-01-17 Initial commit for PCB design - Schematics
2023-01-17 Added footprint for components in Schematics. Updated LED resistors
2023-02-08 Added preliminary PCL layout
2023-02-27 Revision 1 of the board that was manufactured
2023-05-21 Fix NPN BJT Base and emitter pin swap. Attach BS0 to GND to select 4 pin SPI mode for Epaper display. Use 2 side FPC connector
2023-05-21 Create directories to add PCB and software. Modify code running on Development board to run on PCB
2023-05-21 Update readme. Add script to transform images to be displayed on E-paper screen
2023-05-21 Add schematic for circuit and Gerber files for manufacturing PCB
2023-07-29 Add 3d models for PCB and its components
2023-07-29 Add 3d printed files for enclosure. Add BOM and videos to help with assembly
2023-07-29 Added license
